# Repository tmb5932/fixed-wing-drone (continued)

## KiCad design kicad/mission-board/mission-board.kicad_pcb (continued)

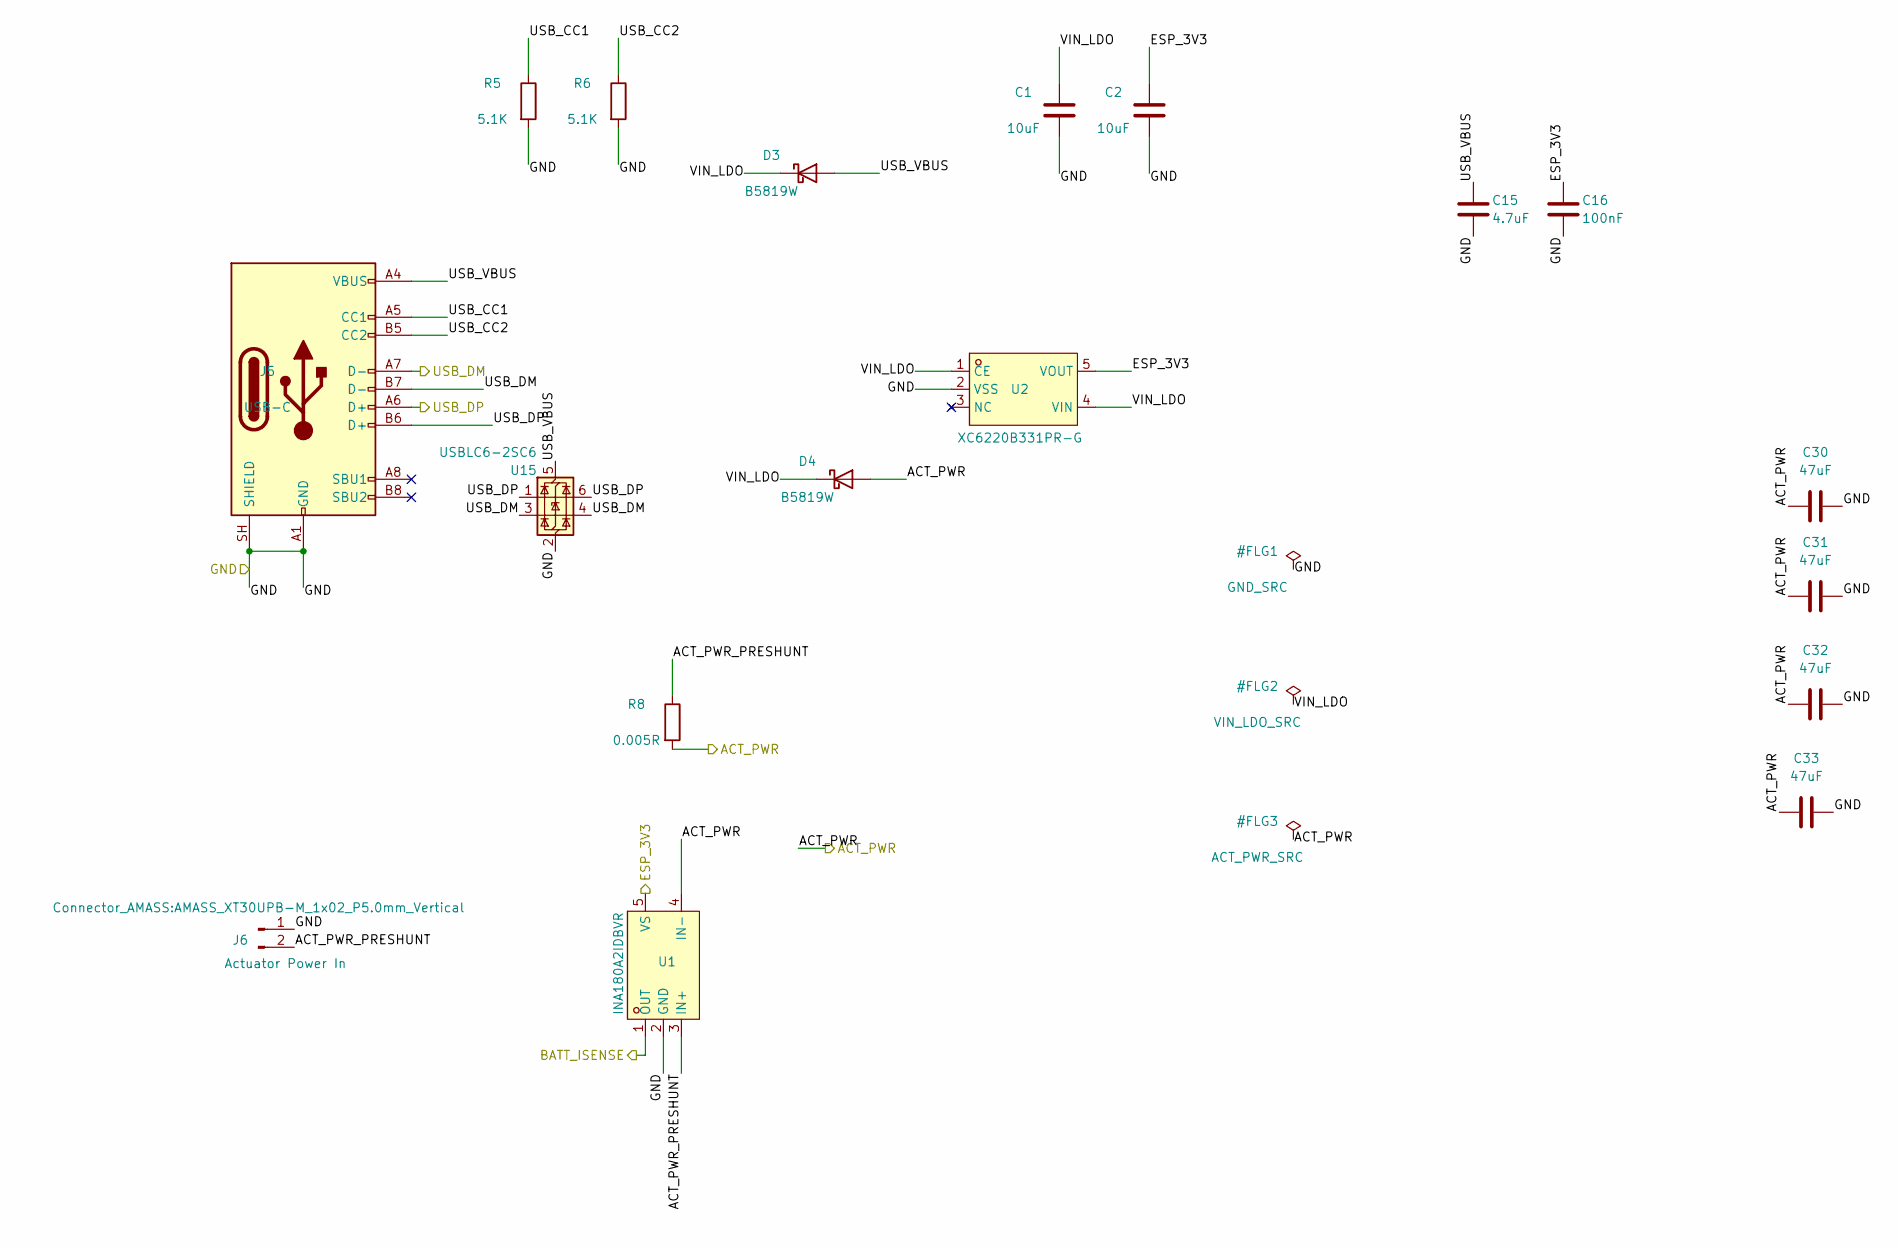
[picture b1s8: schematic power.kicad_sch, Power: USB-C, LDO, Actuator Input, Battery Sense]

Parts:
C1, C2: 10uF; C_0603_1608Metric; LCSC Part C19702
C15: 4.7uF; C_0603_1608Metric; LCSC Part C19666
C16: 100nF; C_0402_1005Metric; LCSC Part C1525
C30, C31, C32, C33: 47uF; C_1206_3216Metric; LCSC Part # C96123
D3, D4: B5819W; D_SOD-123; LCSC Part C8598
J5: USB-C; USB_C_Receptacle_GCT_USB4105-xx-A_16P_TopMnt_Horizontal; LCSC Part C3020560
J6: Actuator Power In; AMASS_XT30UPB-M_1x02_P5.0mm_Vertical; LCSC Part C428721
R5, R6: 5.1K; R_0402_1005Metric; LCSC Part C25905
R8: 0.005R; R_2512_6332Metric; LCSC Part C393074
U1: INA180A2IDBVR; SOT-23-5_L3.0-W1.7-P0.95-LS2.8-BL; LCSC Part C192764
U2: XC6220B331PR-G; SOT-89-5_L4.5-W2.5-P1.50-LS4.4-BR; LCSC Part C3013658
U15: USBLC6-2SC6; SOT-23-6; MPN USBLC6-2SC6; LCSC Part C7519

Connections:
/ACT_PWR: C30.1, C31.1, C32.1, C33.1, D4.2 (A), R8.2, U1.4 (IN-); also elsewhere on the board
/BATT_ISENSE: U1.1 (OUT); also elsewhere on the board
/ESP_3V3: C2.1, C16.1, U1.5 (VS), U2.5 (VOUT); also elsewhere on the board
/GND: C1.2, C2.2, C15.2, C16.2, C30.2, C31.2, C32.2, C33.2, J5.A1 (GND), J5.A12 (GND), J5.B1 (GND), J5.B12 (GND), J5.SH (SHIELD), J6.1, R5.2, R6.2, U1.2 (GND), U2.2 (VSS), U15.2 (GND); also elsewhere on the board
/USB_DM: J5.A7 (D-), J5.B7 (D-), U15.3 (I/O2), U15.4 (I/O2); also elsewhere on the board
/USB_DP: J5.A6 (D+), J5.B6 (D+), U15.1 (I/O1), U15.6 (I/O1); also elsewhere on the board
/power/ACT_PWR_PRESHUNT: J6.2, R8.1, U1.3 (IN+)
/power/USB_CC1: J5.A5 (CC1), R5.1
/power/USB_CC2: J5.B5 (CC2), R6.1
/power/USB_VBUS: C15.1, D3.2 (A), J5.A4 (VBUS), J5.A9 (VBUS), J5.B4 (VBUS), J5.B9 (VBUS), U15.5 (VBUS)
/power/VIN_LDO: C1.1, D3.1 (K), D4.1 (K), U2.1 (CE), U2.4 (VIN)

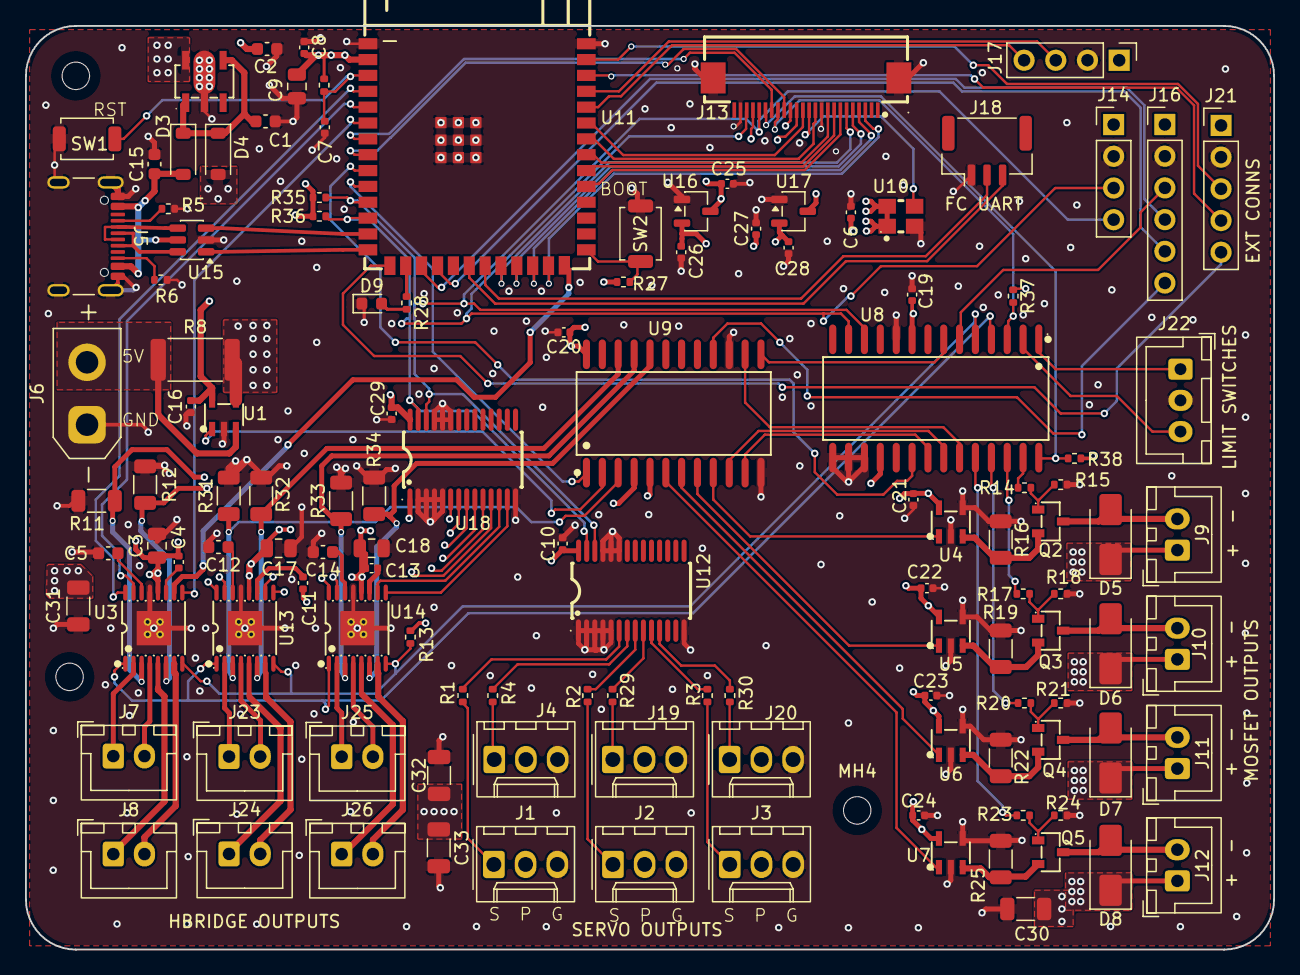
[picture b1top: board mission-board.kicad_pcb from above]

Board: 4 copper layers, 100.0 x 74.0 mm, 127 parts (0 on the bottom side), 122 nets.

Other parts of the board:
MH1, MH3, MH4: MountingHole_2.2mm_M2

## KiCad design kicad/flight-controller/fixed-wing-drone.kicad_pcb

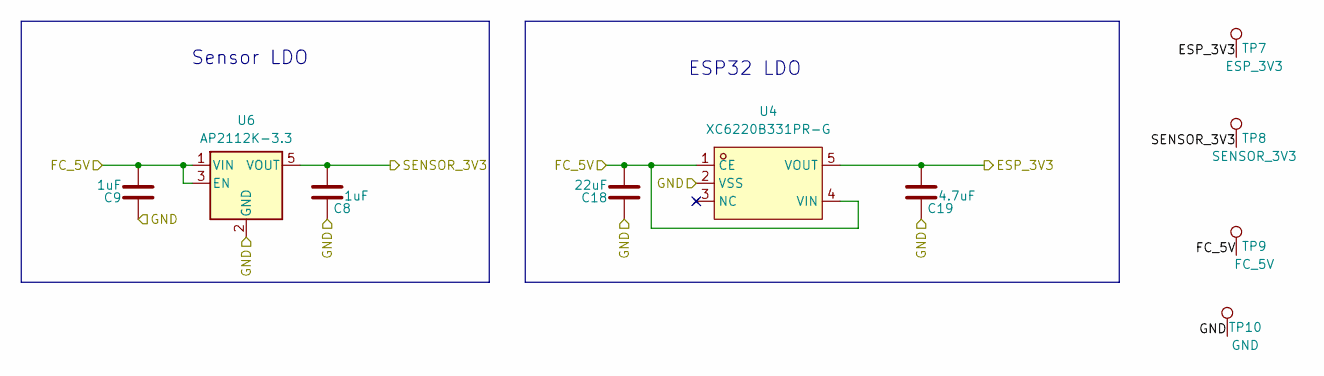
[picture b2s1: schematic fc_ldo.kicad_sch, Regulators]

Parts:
C8, C9: 1uF; C_0402_1005Metric; LCSC Part C14445
C18: 22uF; C_0805_2012Metric; LCSC Part C45783
C19: 4.7uF; C_0603_1608Metric; LCSC Part C1705
TP7: ESP_3V3; TestPoint_Pad_D1.0mm
TP8: SENSOR_3V3; TestPoint_Pad_D1.0mm
TP9: FC_5V; TestPoint_THTPad_D1.5mm_Drill0.7mm
TP10: GND; TestPoint_THTPad_D1.0mm_Drill0.5mm
U4: XC6220B331PR-G; SOT-89-5_L4.5-W2.5-P1.50-LS4.4-BR; MPN XC6220B331PR-G; LCSC Part C3013658
U6: AP2112K-3.3; SOT-23-5; LCSC Part C51118

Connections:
/ESP_3V3: C19.1, TP7.1 (1_1), U4.5 (VOUT); also elsewhere on the board
/FC_5V: C9.2, C18.2, TP9.1 (1_1), U4.1 (CE), U4.4 (VIN), U6.1 (VIN), U6.3 (EN); also elsewhere on the board
/SENSOR_3V3: C8.1, TP8.1 (1_1), U6.5 (VOUT); also elsewhere on the board
GND: C8.2, C9.1, C18.1, C19.2, TP10.1 (1_1), U4.2 (VSS), U6.2 (GND); also elsewhere on the board

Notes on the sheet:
Sensor LDO
ESP32 LDO

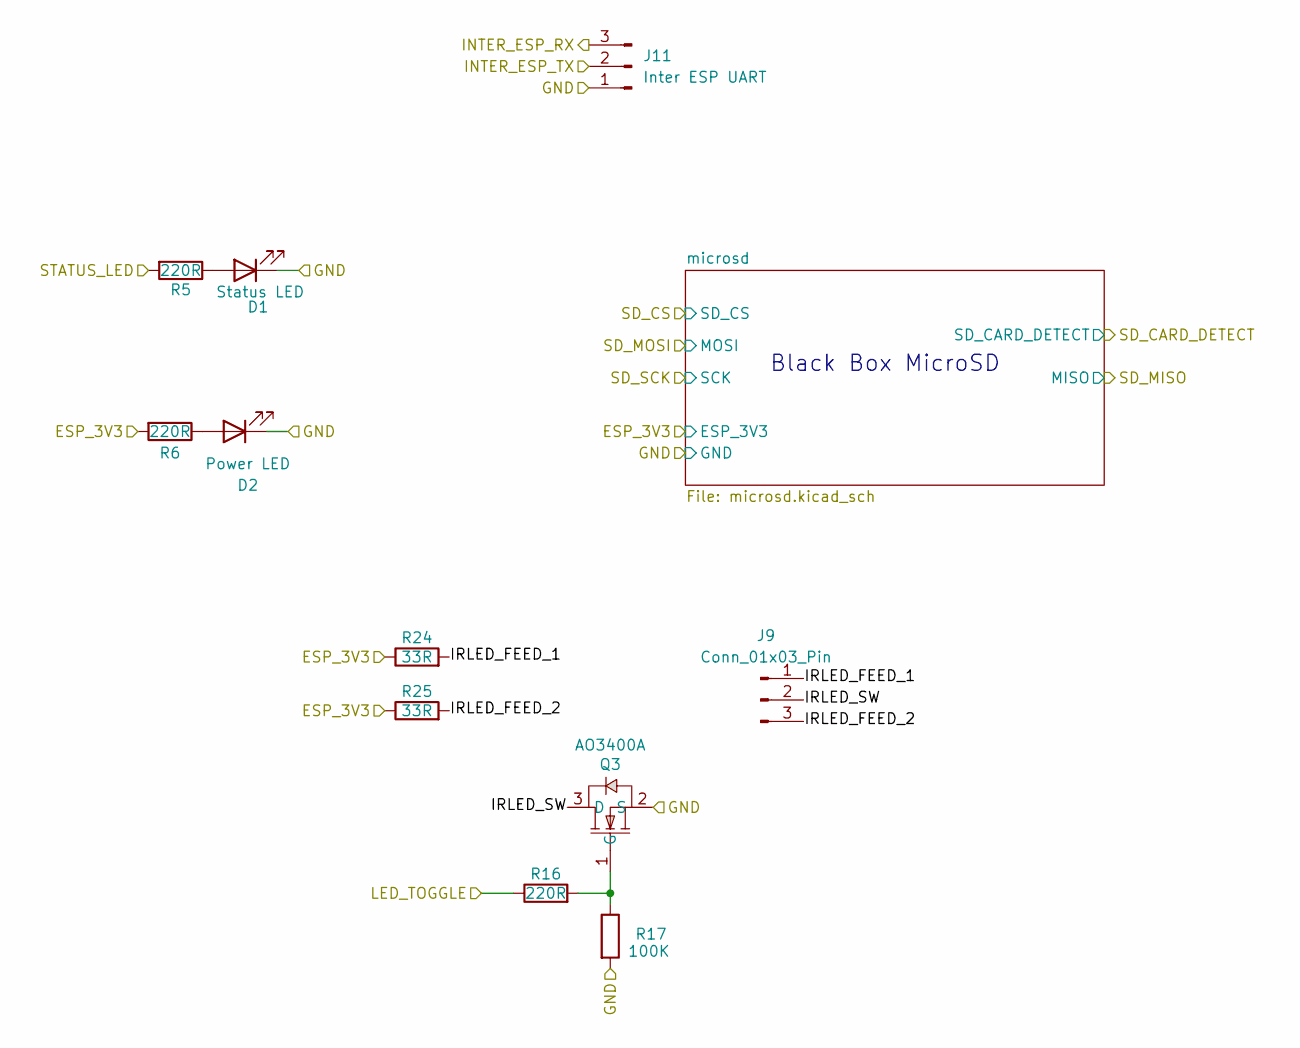
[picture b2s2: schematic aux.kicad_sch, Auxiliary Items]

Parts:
D1: Status LED; LED_0603_1608Metric; LCSC Part C2289
D2: Power LED; LED_0603_1608Metric; LCSC Part C2286
J9: Conn_01x03_Pin; JST_GH_BM03B-GHS-TBT_1x03-1MP_P1.25mm_Vertical; LCSC Part C161691
J11: Inter ESP UART; JST_GH_BM03B-GHS-TBT_1x03-1MP_P1.25mm_Vertical; LCSC Part C161691
Q3: AO3400A; SOT-23-3_L2.9-W1.3-P1.90-LS2.4-BR; LCSC Part C20917
R5, R6, R16: 220R; R_0402_1005Metric; LCSC Part C25091
R17: 100K; R_0402_1005Metric; LCSC Part C25741
R24, R25: 33R; R_1206_3216Metric; LCSC Part C5759775

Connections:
/ESP_3V3: R6.2, R24.1, R25.1; also elsewhere on the board
/INTER_ESP_RX: J11.3; also elsewhere on the board
/INTER_ESP_TX: J11.2; also elsewhere on the board
/LED_TOGGLE: R16.1; also elsewhere on the board
/STATUS_LED: R5.2; also elsewhere on the board
/aux/IRLED_FEED_1: J9.1, R24.2
/aux/IRLED_FEED_2: J9.3, R25.2
/aux/IRLED_SW: J9.2, Q3.3 (D)
GND: D1.1 (K), D2.1 (K), J11.1, Q3.2 (S), R17.2; also elsewhere on the board
unnamed: D1.2 (A), R5.1
unnamed: D2.2 (A), R6.1
unnamed: Q3.1 (G), R16.2, R17.1

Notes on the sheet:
Black Box MicroSD

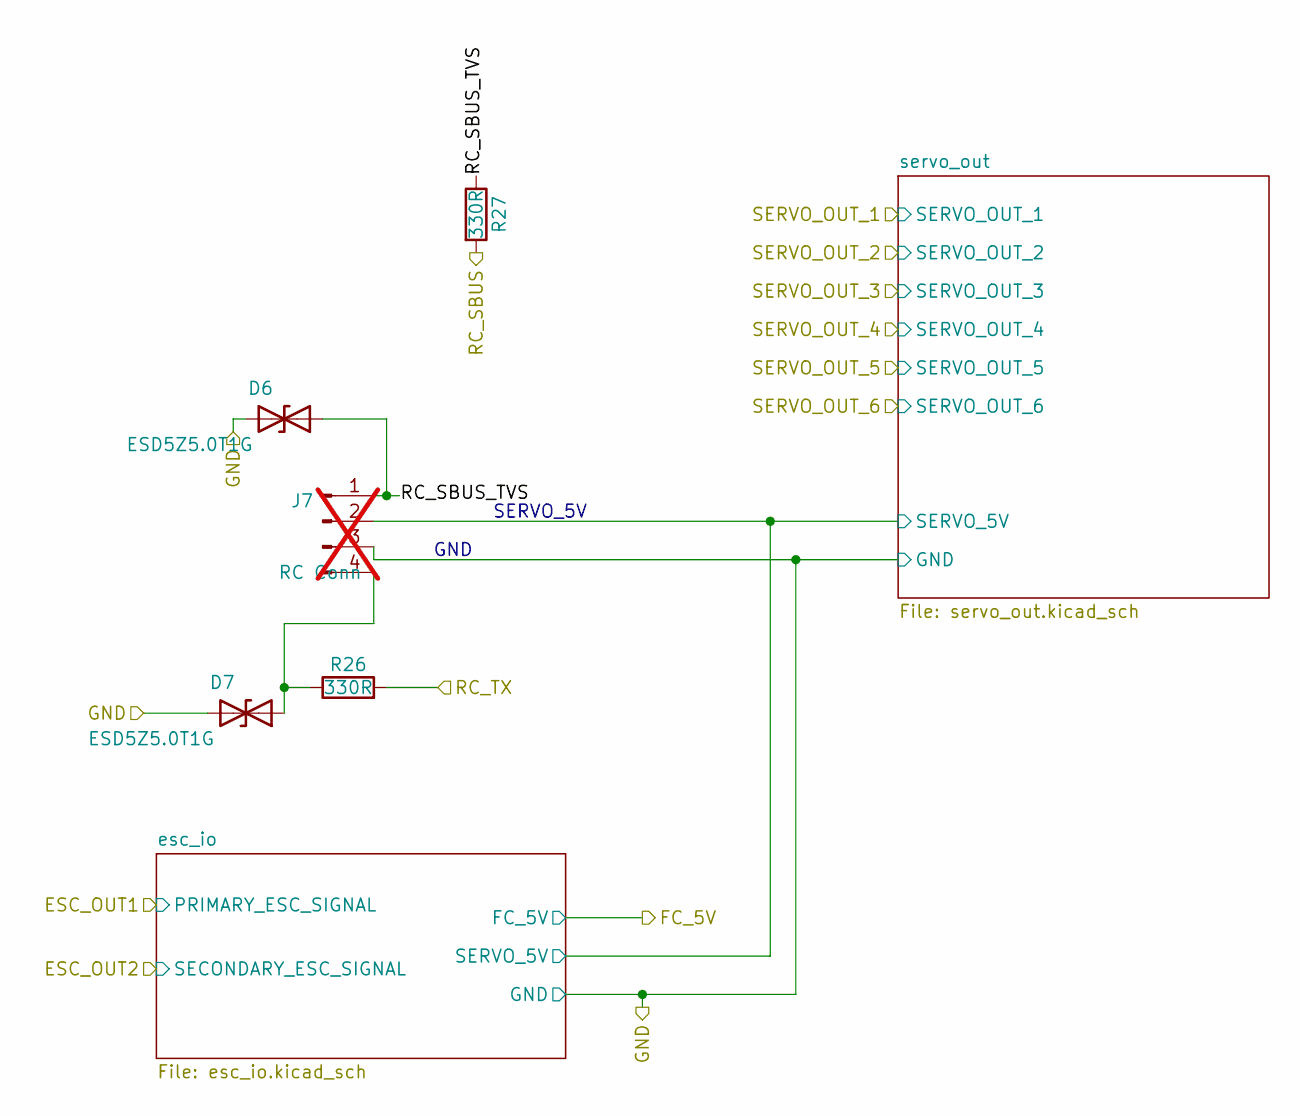
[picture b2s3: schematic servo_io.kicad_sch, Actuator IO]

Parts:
D6, D7: ESD5Z5.0T1G; D_SOD-523; LCSC Part C82044
J7: RC Conn; Molex_KK-254_AE-6410-04A_1x04_P2.54mm_Vertical; MPN 0022232041; not fitted
R26, R27: 330R; R_0402_1005Metric; LCSC Part C25104

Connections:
/RC_SBUS: R27.2; also elsewhere on the board
/RC_TX: R26.2; also elsewhere on the board
/actuator_io/RC_SBUS_TVS: D6.1 (A1), J7.1, R27.1
/actuator_io/esc_io/SERVO_5V: J7.2; also elsewhere on the board
GND: D6.2 (A2), D7.2 (A2), J7.3; also elsewhere on the board
unnamed: D7.1 (A1), J7.4, R26.1

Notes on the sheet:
SERVO_5V
GND

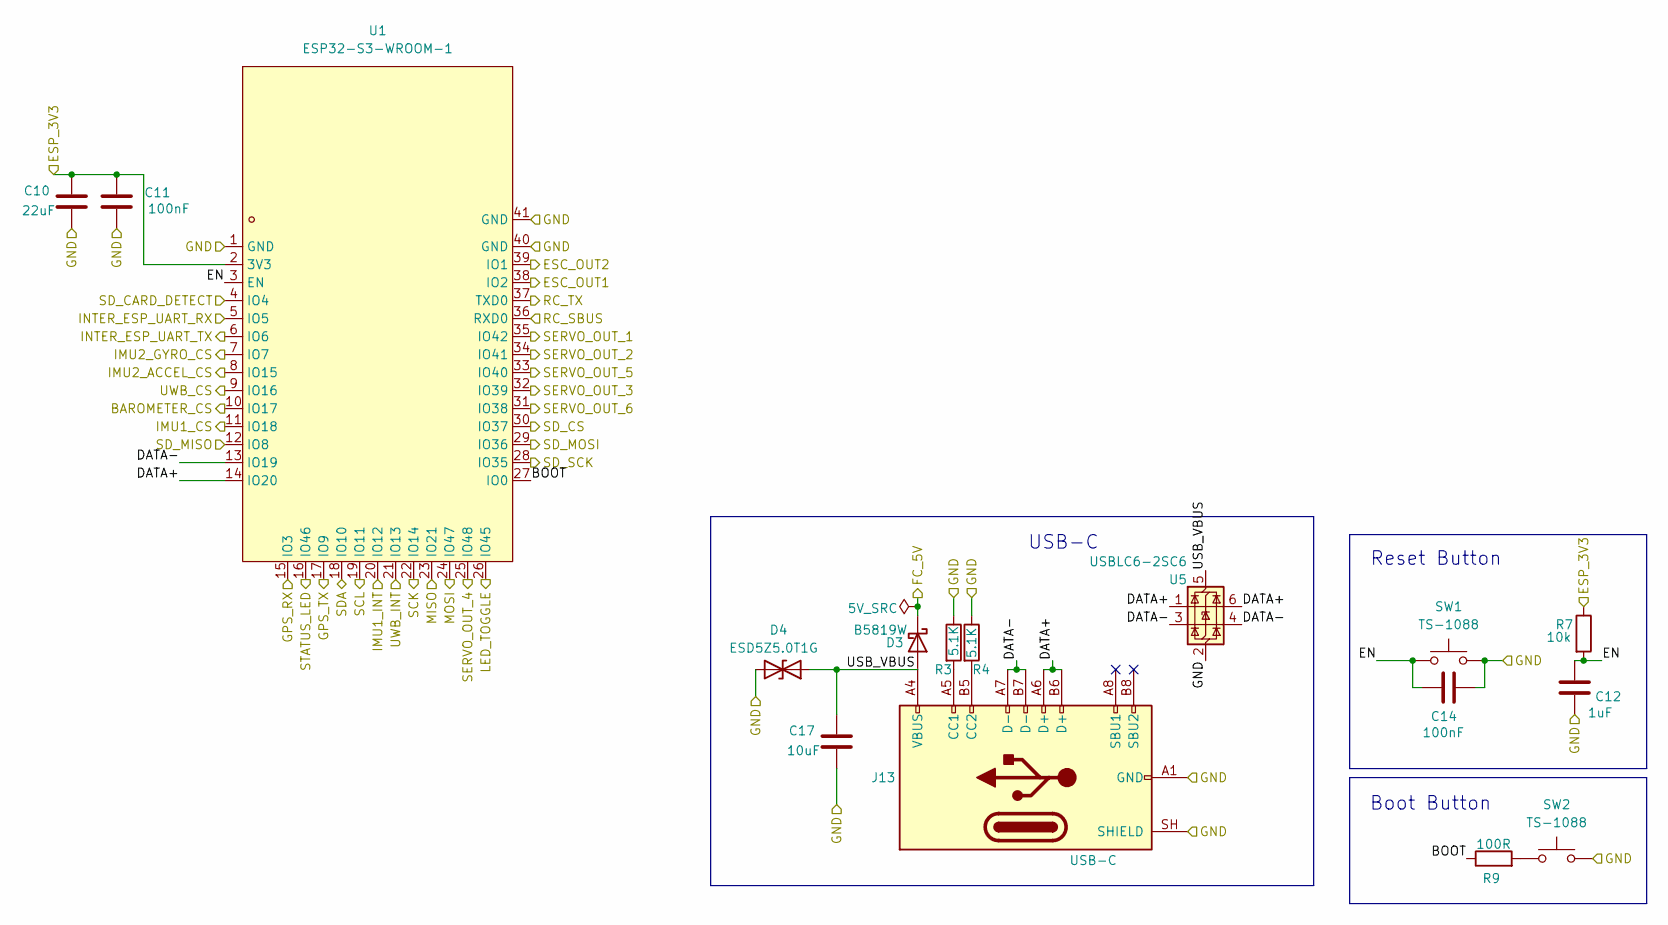
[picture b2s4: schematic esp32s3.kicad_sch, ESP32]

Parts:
C10: 22uF; C_0805_2012Metric; LCSC Part C45783
C11, C14: 100nF; C_0402_1005Metric; LCSC Part C1525
C12: 1uF; C_0402_1005Metric; LCSC Part C14445
C17: 10uF; C_0805_2012Metric; LCSC Part C440198
D3: B5819W; D_SOD-123; LCSC Part C8598
D4: ESD5Z5.0T1G; D_SOD-523; LCSC Part C82044
J13: USB-C; USB_C_Receptacle_GCT_USB4105-xx-A_16P_TopMnt_Horizontal; LCSC Part C3020560
R3, R4: 5.1K; R_0402_1005Metric; LCSC Part C25905
R7: 10k; R_0402_1005Metric; LCSC Part C25531
R9: 100R; R_0402_1005Metric; LCSC Part C25076
SW1, SW2: TS-1088; SW_SPST_TS-1088-xR020; LCSC Part C720477
U1: ESP32-S3-WROOM-1; WIRELM-SMD_ESP32-S3-WROOM-1; MPN ESP32-S3-WROOM-1-N16R2; LCSC Part C2913205
U5: USBLC6-2SC6; SOT-23-6; MPN USBLC6-2SC6; LCSC Part C7519

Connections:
/BAROMETER_CS: U1.10 (IO17); also elsewhere on the board
/ESC_OUT1: U1.38 (IO2); also elsewhere on the board
/ESC_OUT2: U1.39 (IO1); also elsewhere on the board
/ESP_3V3: C10.1, C11.1, R7.1, U1.2 (3V3); also elsewhere on the board
/FC_5V: D3.1 (K); also elsewhere on the board
/GPS_RX: U1.15 (IO3); also elsewhere on the board
/GPS_TX: U1.17 (IO9); also elsewhere on the board
/IMU1_CS: U1.11 (IO18); also elsewhere on the board
/IMU1_INT: U1.20 (IO12); also elsewhere on the board
/IMU2_ACCEL_CS: U1.8 (IO15); also elsewhere on the board
/IMU2_GYRO_CS: U1.7 (IO7); also elsewhere on the board
/INTER_ESP_RX: U1.5 (IO5); also elsewhere on the board
/INTER_ESP_TX: U1.6 (IO6); also elsewhere on the board
/LED_TOGGLE: U1.26 (IO45); also elsewhere on the board
/MISO: U1.23 (IO21); also elsewhere on the board
/MOSI: U1.24 (IO47); also elsewhere on the board
/RC_SBUS: U1.36 (RXD0); also elsewhere on the board
/RC_TX: U1.37 (TXD0); also elsewhere on the board
/SCK: U1.22 (IO14); also elsewhere on the board
/SCL: U1.19 (IO11); also elsewhere on the board
/SDA: U1.18 (IO10); also elsewhere on the board
/SD_CARD_DETECT: U1.4 (IO4); also elsewhere on the board
/SD_CS: U1.30 (IO37); also elsewhere on the board
/SD_MISO: U1.12 (IO8); also elsewhere on the board
/SD_MOSI: U1.29 (IO36); also elsewhere on the board
/SD_SCK: U1.28 (IO35); also elsewhere on the board
/SERVO_OUT_1: U1.35 (IO42); also elsewhere on the board
/SERVO_OUT_2: U1.34 (IO41); also elsewhere on the board
/SERVO_OUT_3: U1.32 (IO39); also elsewhere on the board
/SERVO_OUT_4: U1.25 (IO48); also elsewhere on the board
/SERVO_OUT_5: U1.33 (IO40); also elsewhere on the board
/SERVO_OUT_6: U1.31 (IO38); also elsewhere on the board
/STATUS_LED: U1.16 (IO46); also elsewhere on the board
/UWB_CS: U1.9 (IO16); also elsewhere on the board
/UWB_INT: U1.21 (IO13); also elsewhere on the board
/esp32s3/BOOT: R9.1, U1.27 (IO0)
/esp32s3/DATA+: J13.A6 (D+), J13.B6 (D+), U1.14 (IO20), U5.1 (I/O1), U5.6 (I/O1)
/esp32s3/DATA-: J13.A7 (D-), J13.B7 (D-), U1.13 (IO19), U5.3 (I/O2), U5.4 (I/O2)
/esp32s3/EN: C12.1, C14.1, R7.2, SW1.1, U1.3 (EN)
/esp32s3/USB_VBUS: C17.1, D3.2 (A), D4.1 (A1), J13.A4 (VBUS), J13.A9 (VBUS), J13.B4 (VBUS), J13.B9 (VBUS), U5.5 (VBUS)
GND: C10.2, C11.2, C12.2, C14.2, C17.2, D4.2 (A2), J13.A1 (GND), J13.A12 (GND), J13.B1 (GND), J13.B12 (GND), J13.SH (SHIELD), R3.1, R4.1, SW1.2, SW2.2, U1.1 (GND), U1.40 (GND), U1.41 (GND), U5.2 (GND); also elsewhere on the board
unnamed: J13.A5 (CC1), R3.2
unnamed: J13.B5 (CC2), R4.2
unnamed: R9.2, SW2.1

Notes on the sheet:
Boot Button
Reset Button
USB-C

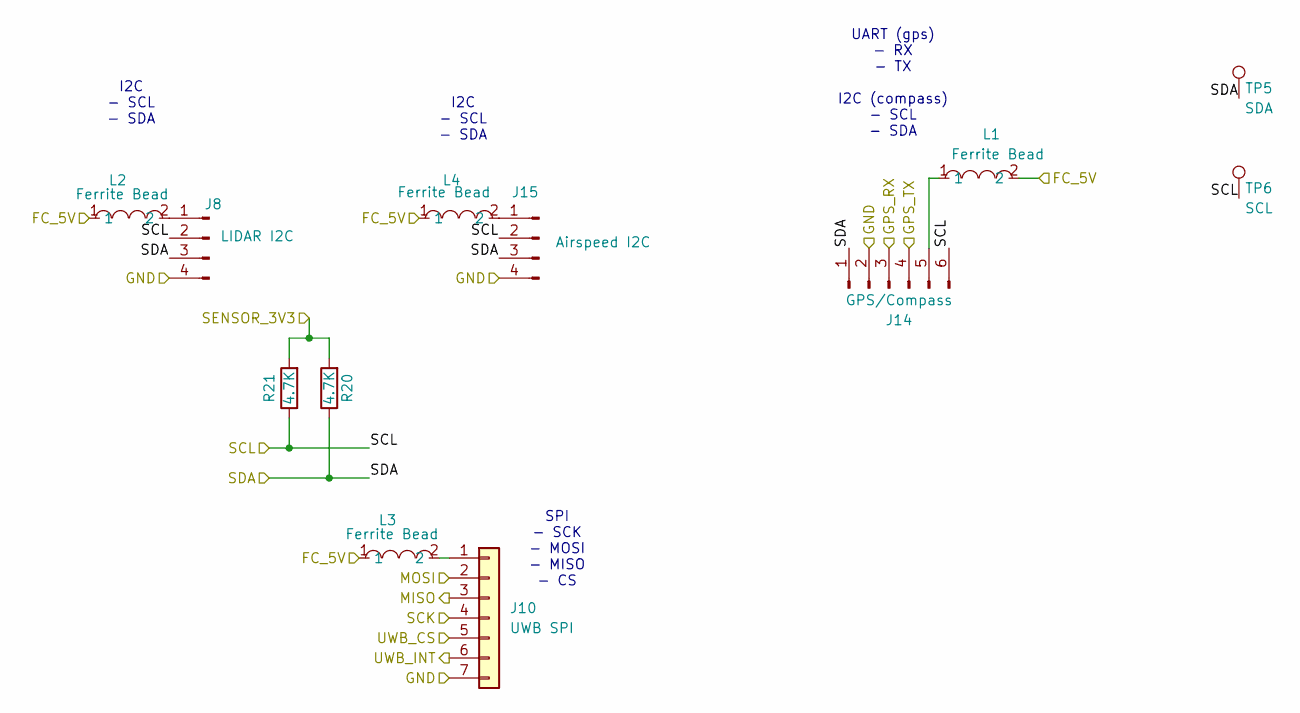
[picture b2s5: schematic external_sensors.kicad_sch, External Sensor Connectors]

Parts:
J8: LIDAR I2C; Molex_PicoBlade_53398-0471_1x04-1MP_P1.25mm_Vertical; LCSC Part C17617036
J10: UWB SPI; JST_GH_BM07B-GHS-TBT_1x07-1MP_P1.25mm_Vertical; LCSC Part C378970
J14: GPS/Compass; JST_GH_BM06B-GHS-TBT_1x06-1MP_P1.25mm_Vertical; LCSC Part C189892
J15: Airspeed I2C; JST_GH_BM04B-GHS-TBT_1x04-1MP_P1.25mm_Vertical; LCSC Part C161692
L1, L2, L3, L4: Ferrite Bead; L0603; MPN BLM18PG121SN1D; LCSC Part C14709
R20, R21: 4.7K; R_0402_1005Metric; LCSC Part C25900
TP5: SDA; TestPoint_THTPad_D1.0mm_Drill0.5mm
TP6: SCL; TestPoint_THTPad_D1.0mm_Drill0.5mm

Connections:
/FC_5V: L1.2, L2.1, L3.1, L4.1; also elsewhere on the board
/GPS_RX: J14.3; also elsewhere on the board
/GPS_TX: J14.4; also elsewhere on the board
/MISO: J10.3; also elsewhere on the board
/MOSI: J10.2; also elsewhere on the board
/SCK: J10.4; also elsewhere on the board
/SCL: J8.2, J14.6, J15.2, R21.1, TP6.1 (1_1); also elsewhere on the board
/SDA: J8.3, J14.1, J15.3, R20.1, TP5.1 (1_1); also elsewhere on the board
/SENSOR_3V3: R20.2, R21.2; also elsewhere on the board
/UWB_CS: J10.5; also elsewhere on the board
/UWB_INT: J10.6; also elsewhere on the board
GND: J8.4, J10.7, J14.2, J15.4; also elsewhere on the board
unnamed: J8.1, L2.2
unnamed: J10.1, L3.2
unnamed: J14.5, L1.1
unnamed: J15.1, L4.2

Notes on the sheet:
I2C - SCL - SDA
UART (gps) - RX - TX I2C (compass) - SCL - SDA
SPI - SCK - MOSI - MISO - CS

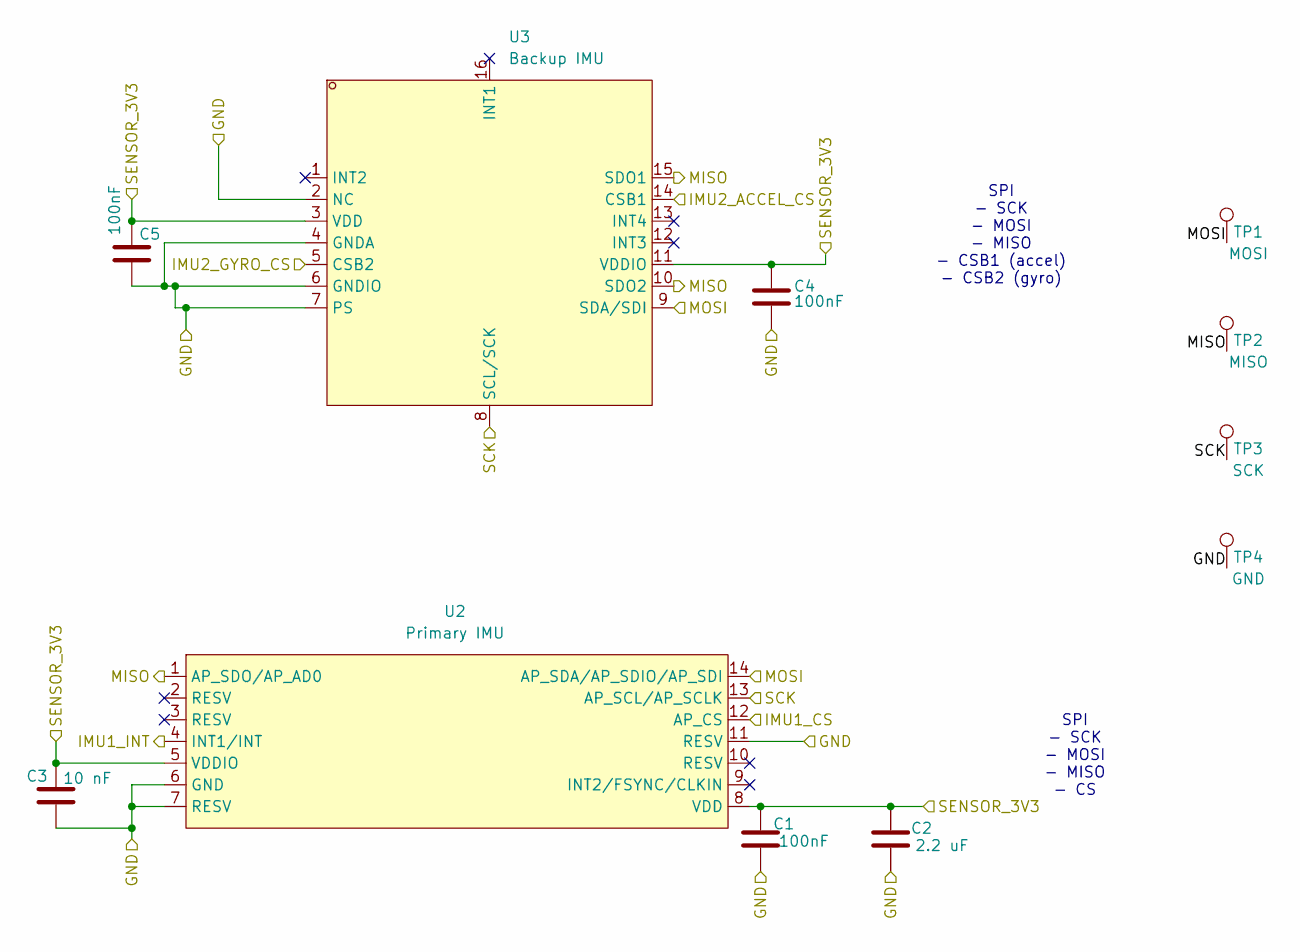
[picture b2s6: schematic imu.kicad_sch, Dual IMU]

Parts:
C1, C4, C5: 100nF; C_0402_1005Metric; LCSC Part C1525
C2: 2.2 uF; C_0603_1608Metric; LCSC Part C23630
C3: 10 nF; C_0402_1005Metric; LCSC Part C15195
TP1: MOSI; TestPoint_THTPad_D1.0mm_Drill0.5mm
TP2: MISO; TestPoint_THTPad_D1.0mm_Drill0.5mm
TP3: SCK; TestPoint_THTPad_D1.0mm_Drill0.5mm
TP4: GND; TestPoint_THTPad_D1.5mm_Drill0.7mm
U2: Primary IMU; LGA-14_L3.0-W2.5-P0.50-TL; MPN ICM-42688-P; LCSC Part C1850418
U3: Backup IMU; LGA-16_L4.5-W3.0-P0.50-BL; MPN BMI088; LCSC Part C194919

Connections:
/IMU1_CS: U2.12 (AP_CS); also elsewhere on the board
/IMU1_INT: U2.4 (INT1/INT); also elsewhere on the board
/IMU2_ACCEL_CS: U3.14 (CSB1); also elsewhere on the board
/IMU2_GYRO_CS: U3.5 (CSB2); also elsewhere on the board
/MISO: TP2.1 (1_1), U2.1 (AP_SDO/AP_AD0), U3.10 (SDO2), U3.15 (SDO1); also elsewhere on the board
/MOSI: TP1.1 (1_1), U2.14 (AP_SDA/AP_SDIO/AP_SDI), U3.9 (SDA/SDI); also elsewhere on the board
/SCK: TP3.1 (1_1), U2.13 (AP_SCL/AP_SCLK), U3.8 (SCL/SCK); also elsewhere on the board
/SENSOR_3V3: C1.1, C2.1, C3.1, C4.1, C5.1, U2.5 (VDDIO), U2.8 (VDD), U3.3 (VDD), U3.11 (VDDIO); also elsewhere on the board
GND: C1.2, C2.2, C3.2, C4.2, C5.2, TP4.1 (1_1), U2.6 (GND), U2.7 (RESV), U2.11 (RESV), U3.2 (NC), U3.4 (GNDA), U3.6 (GNDIO), U3.7 (PS); also elsewhere on the board

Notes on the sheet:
SPI - SCK - MOSI - MISO - CSB1 (accel) - CSB2 (gyro)
SPI - SCK - MOSI - MISO - CS

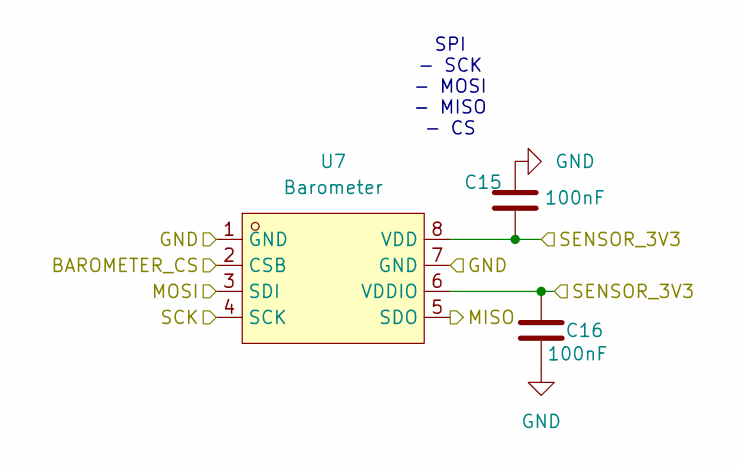
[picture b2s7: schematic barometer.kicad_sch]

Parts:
C15, C16: 100nF; C_0402_1005Metric; LCSC Part C1525
U7: Barometer; LGA-8_L2.5-W2.0-P0.65-TR_DPS368; MPN DPS368XTSA1; LCSC Part C3232508

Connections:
/BAROMETER_CS: U7.2 (CSB); also elsewhere on the board
/MISO: U7.5 (SDO); also elsewhere on the board
/MOSI: U7.3 (SDI); also elsewhere on the board
/SCK: U7.4 (SCK); also elsewhere on the board
/SENSOR_3V3: C15.2, C16.1, U7.6 (VDDIO), U7.8 (VDD); also elsewhere on the board
GND: C15.1, C16.2, U7.1 (GND), U7.7 (GND); also elsewhere on the board

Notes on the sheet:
SPI - SCK - MOSI - MISO - CS

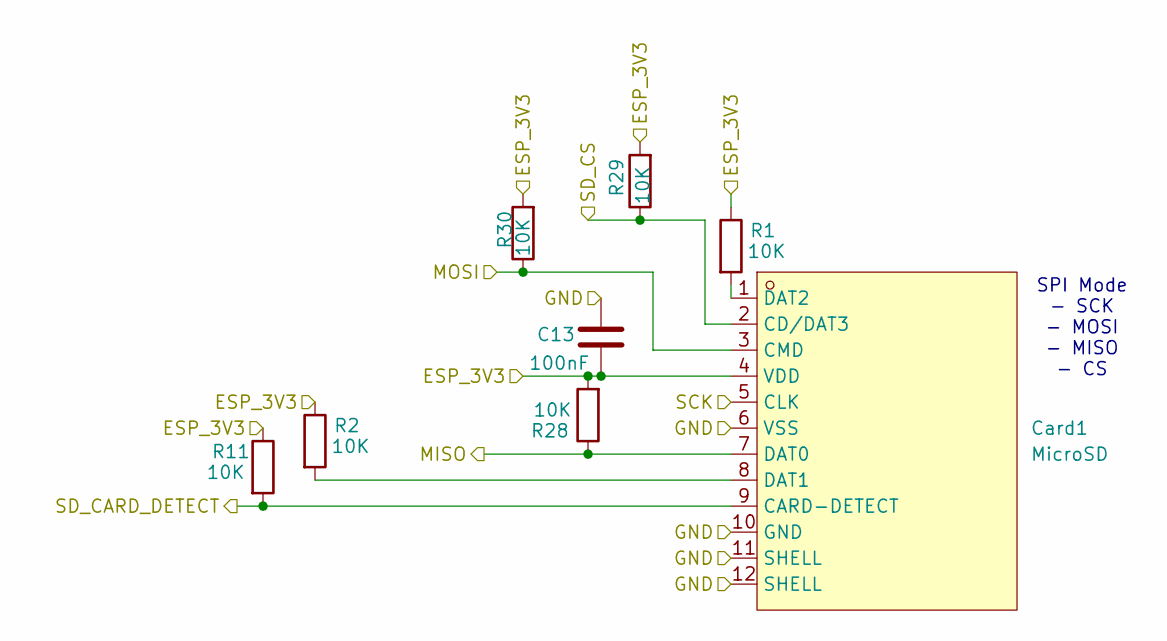
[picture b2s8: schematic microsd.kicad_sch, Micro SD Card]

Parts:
C13: 100nF; C_0402_1005Metric; LCSC Part C1525
Card1: MicroSD; TF-SMD_XKTF-001B; MPN XKTF-001B; LCSC Part C381080
R1, R2, R11, R28, R29, R30: 10K; R_0402_1005Metric; LCSC Part C25531

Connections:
/ESP_3V3: C13.2, Card1.4 (VDD), R1.1, R2.1, R11.1, R28.2, R29.2, R30.2; also elsewhere on the board
/SD_CARD_DETECT: Card1.9 (CARD-DETECT), R11.2; also elsewhere on the board
/SD_CS: Card1.2 (CD/DAT3), R29.1; also elsewhere on the board
/SD_MISO: Card1.7 (DAT0), R28.1; also elsewhere on the board
/SD_MOSI: Card1.3 (CMD), R30.1; also elsewhere on the board
/SD_SCK: Card1.5 (CLK); also elsewhere on the board
GND: C13.1, Card1.6 (VSS), Card1.10 (GND), Card1.11 (SHELL), Card1.12 (SHELL); also elsewhere on the board
unnamed: Card1.8 (DAT1), R2.2
unnamed: Card1.1 (DAT2), R1.2

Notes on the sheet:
SPI Mode - SCK - MOSI - MISO - CS

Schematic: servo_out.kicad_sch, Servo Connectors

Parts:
J1: 1; Molex_KK-254_AE-6410-03A_1x03_P2.54mm_Vertical; not fitted
J2: 2; Molex_KK-254_AE-6410-03A_1x03_P2.54mm_Vertical; not fitted
J3: 3; Molex_KK-254_AE-6410-03A_1x03_P2.54mm_Vertical; not fitted
J4: 4; Molex_KK-254_AE-6410-03A_1x03_P2.54mm_Vertical; not fitted
J5: 5; Molex_KK-254_AE-6410-03A_1x03_P2.54mm_Vertical; not fitted
J6: 6; Molex_KK-254_AE-6410-03A_1x03_P2.54mm_Vertical; not fitted
R12, R13, R14, R15, R18, R19: 330R; R_0402_1005Metric; LCSC Part C25104

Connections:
/SERVO_OUT_1: R12.1; also elsewhere on the board
/SERVO_OUT_2: R13.1; also elsewhere on the board
/SERVO_OUT_3: R14.1; also elsewhere on the board
/SERVO_OUT_4: R19.1; also elsewhere on the board
/SERVO_OUT_5: R18.1; also elsewhere on the board
/SERVO_OUT_6: R15.1; also elsewhere on the board
/actuator_io/esc_io/SERVO_5V: J1.2, J2.2, J3.2, J4.2, J5.2, J6.2; also elsewhere on the board
GND: J1.3, J2.3, J3.3, J4.3, J5.3, J6.3; also elsewhere on the board
unnamed: J1.1, R12.2
unnamed: J2.1, R13.2
unnamed: J3.1, R14.2
unnamed: J4.1, R19.2
unnamed: J5.1, R18.2
unnamed: J6.1, R15.2

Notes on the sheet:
Output 4
Output 2
Output 1
Output 6
Output 3
Output 5

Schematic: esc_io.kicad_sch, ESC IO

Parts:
C20: 22uF; C_0805_2012Metric; LCSC Part C45783
D5: B5819W; D_SOD-123; LCSC Part C8598
J19: ESC2; Molex_KK-254_AE-6410-03A_1x03_P2.54mm_Vertical; not fitted
J20: FC UBEC Input; Molex_KK-254_AE-6410-03A_1x03_P2.54mm_Vertical; not fitted
J22: ESC1; Molex_KK-254_AE-6410-03A_1x03_P2.54mm_Vertical; not fitted
R22, R23: 330R; R_0402_1005Metric; LCSC Part C25104

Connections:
/ESC_OUT1: R23.2; also elsewhere on the board
/ESC_OUT2: R22.2; also elsewhere on the board
/FC_5V: D5.1 (K); also elsewhere on the board
/actuator_io/esc_io/SERVO_5V: C20.1, J22.2; also elsewhere on the board
GND: C20.2, J19.3, J20.1, J20.3, J22.3; also elsewhere on the board
unnamed: D5.2 (A), J20.2
unnamed: J19.1, R22.1
unnamed: J22.1, R23.1

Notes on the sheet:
GND
VCC
Only takes 5v from ESC1 to control servos. Doing power OR'ing is not worth it. ESC2 5v line is NC.

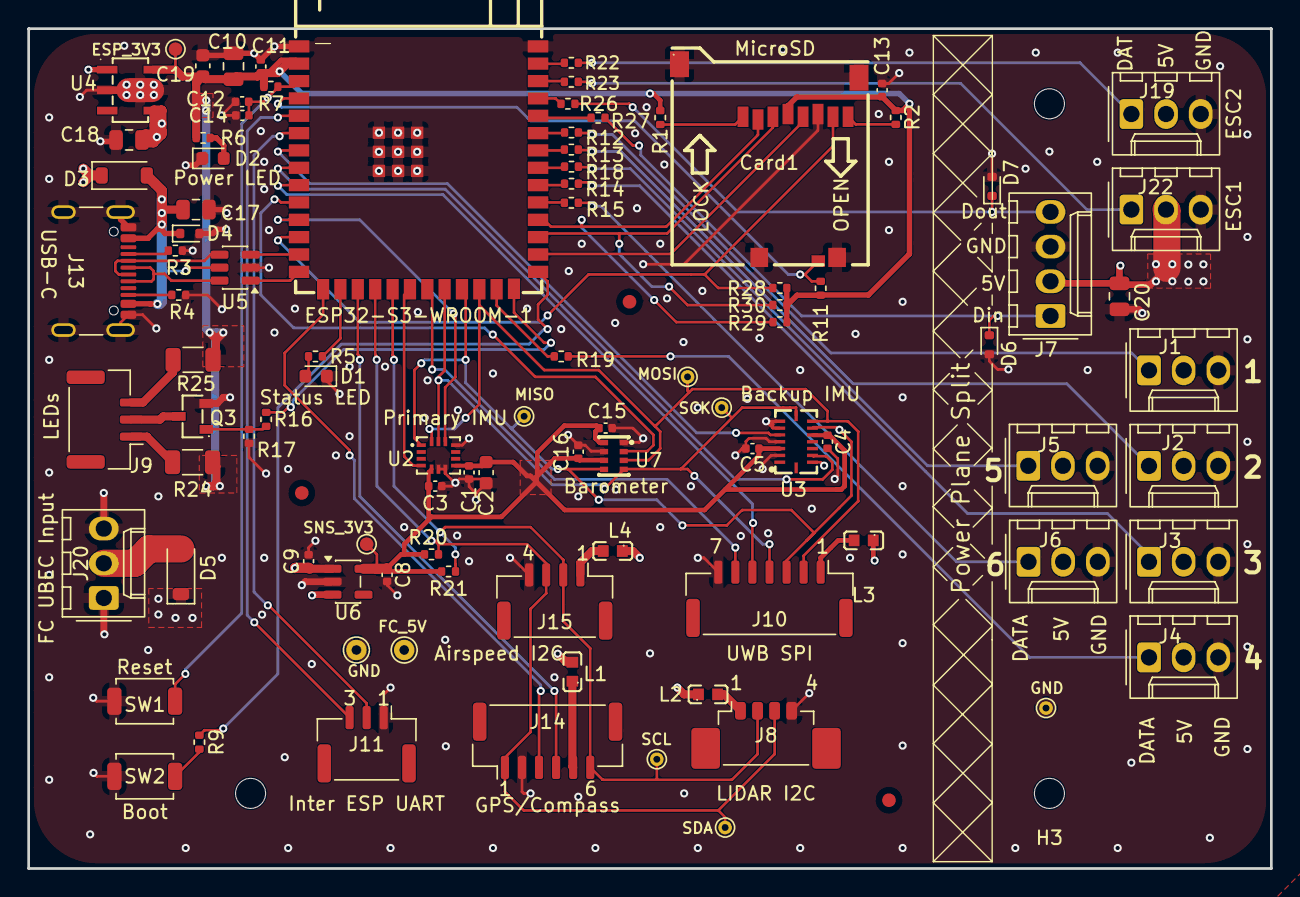
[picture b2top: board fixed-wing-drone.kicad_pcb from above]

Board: 4 copper layers, 91.0 x 61.5 mm, 101 parts (0 on the bottom side), 69 nets.

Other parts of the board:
FID1, FID2, FID3: Fiducial_1mm_Mask2mm
H1, H2, H3: MountingHole_2.2mm_M2
